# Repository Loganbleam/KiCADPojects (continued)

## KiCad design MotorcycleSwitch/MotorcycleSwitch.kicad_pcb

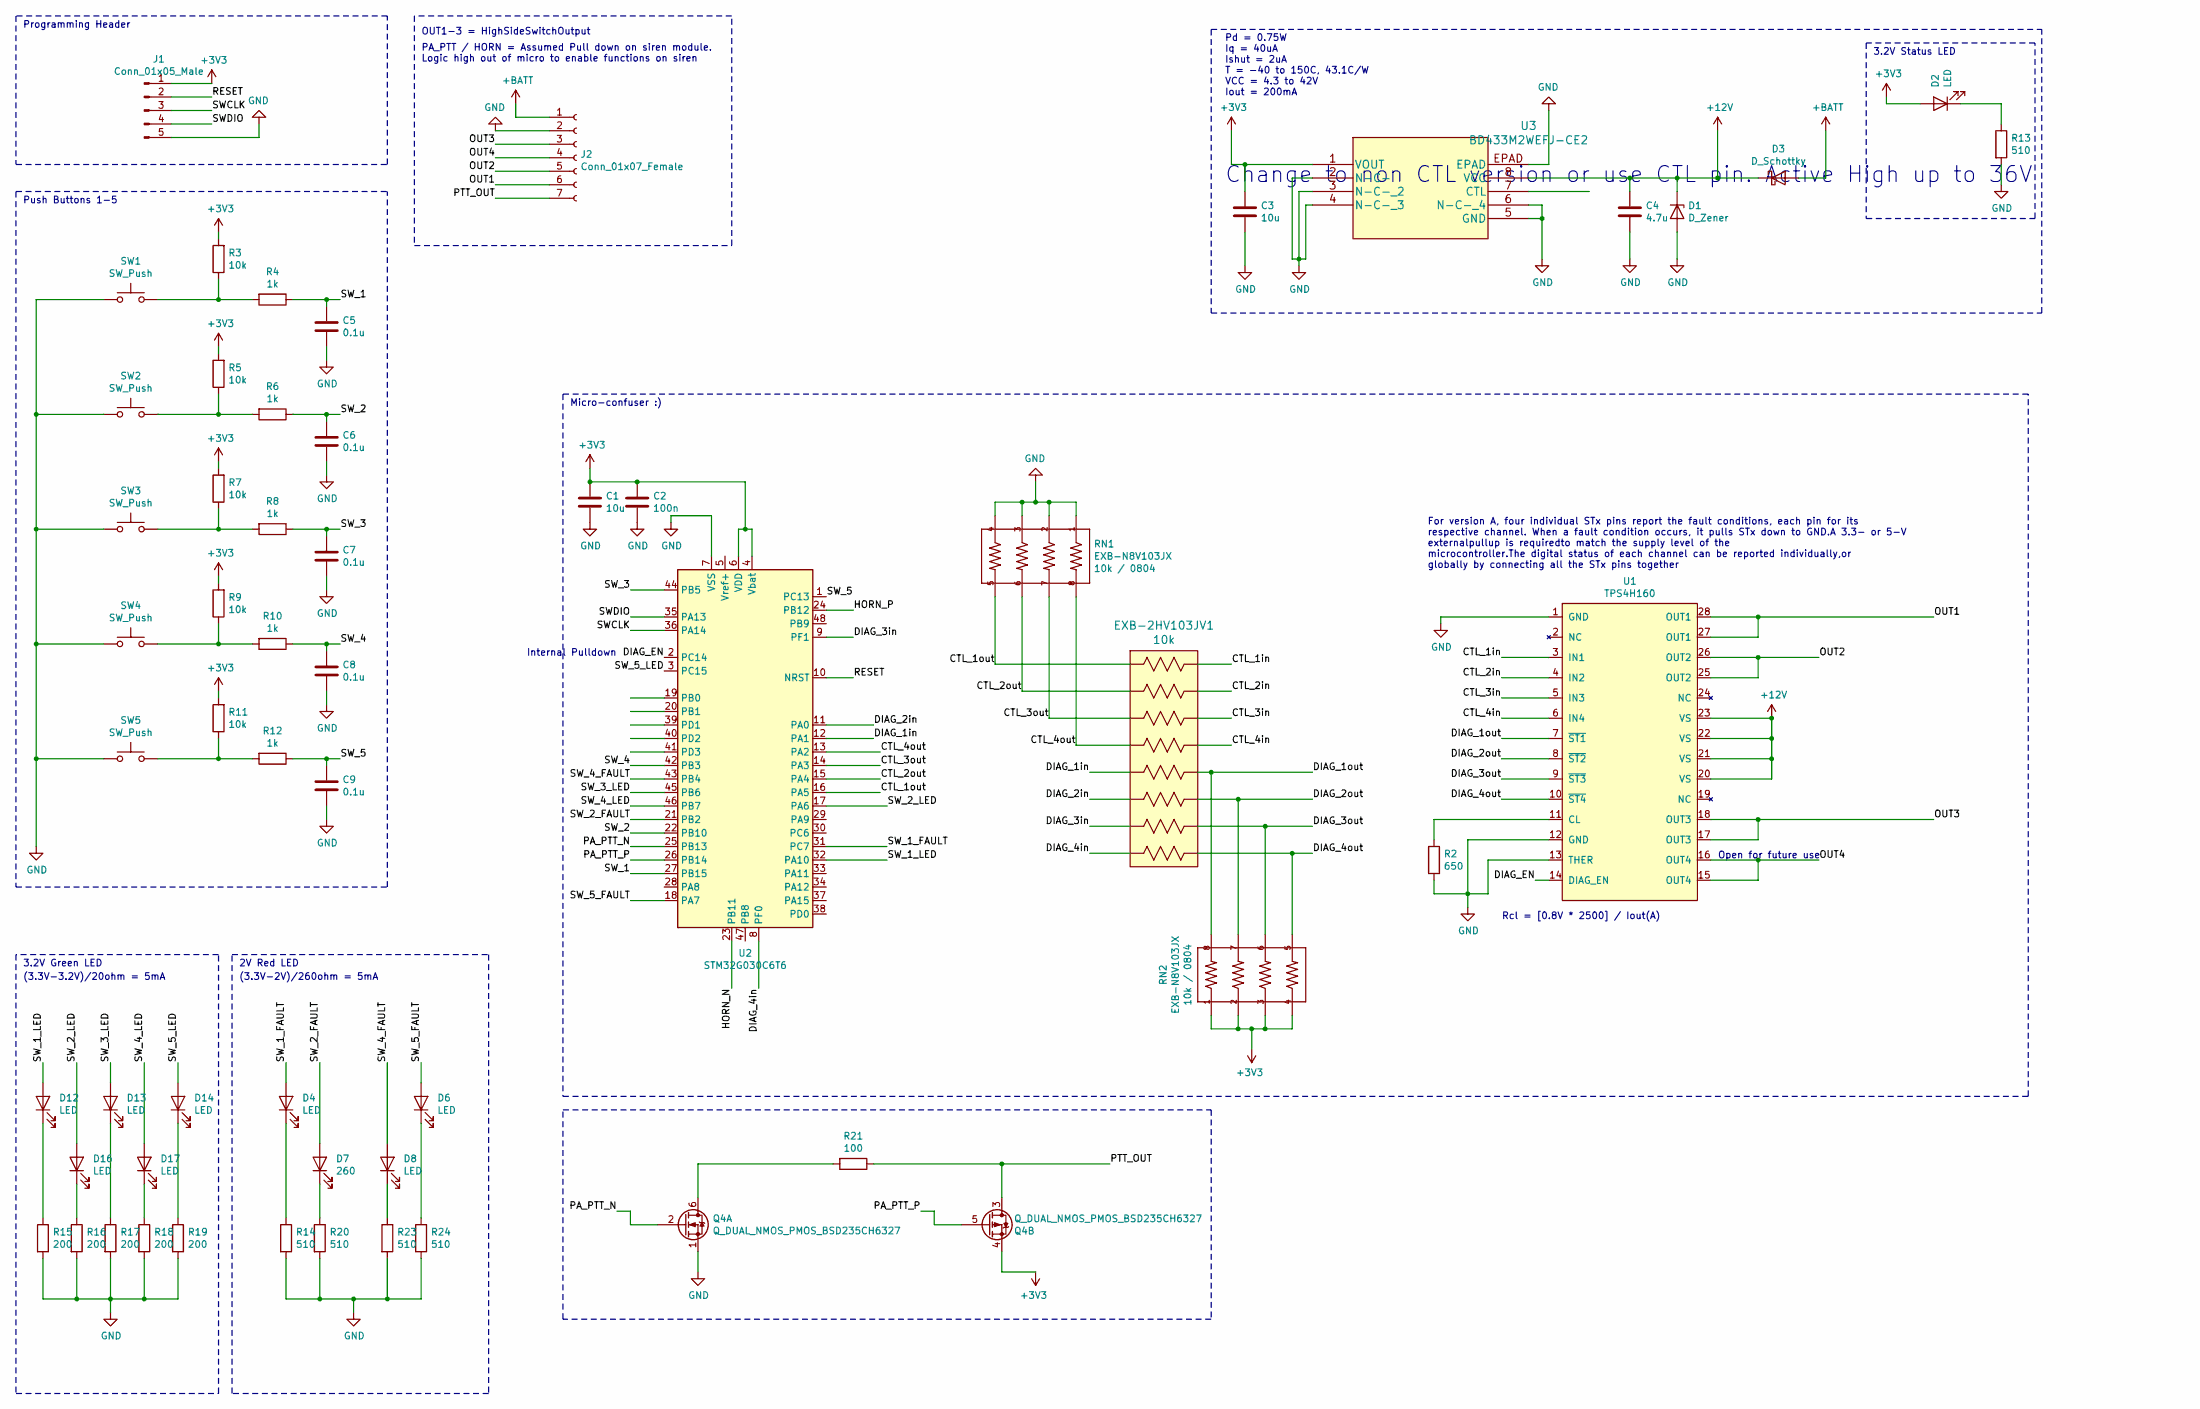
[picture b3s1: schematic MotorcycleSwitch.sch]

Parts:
C1, C3: 10u; C_0603_1608Metric
C2: 100n; C_0603_1608Metric
C4: 4.7u; C_0603_1608Metric
C5, C6, C7, C8, C9: 0.1u; C_0603_1608Metric
D1: D_Zener; D_SOD-123
D2: LED; LED_0603_1608Metric_Castellated
D3: D_Schottky; D_SMA
D4, D6, D8, D12, D13, D14, D16, D17: LED; LED_0603_1608Metric
D7: 260; LED_0603_1608Metric
EXB-2HV103JV1: 10k; EXB-2HV103JV
J1: Conn_01x05_Male; PinHeader_1x05_P2.54mm_Vertical
J2: Conn_01x07_Female; PinHeader_1x07_P2.54mm_Vertical
Q4: Q_DUAL_NMOS_PMOS_BSD235CH6327; SOT-363_SC-70-6
R2: 650; R_0603_1608Metric_Pad1.05x0.95mm_HandSolder
R3, R5, R7, R9, R11: 10k; R_0603_1608Metric
R4, R6, R8, R10, R12: 1k; R_0603_1608Metric
R13, R14, R20, R23, R24: 510; R_0603_1608Metric
R15, R16, R17, R18, R19: 200; R_0603_1608Metric
R21: 100; R_0603_1608Metric
RN1, RN2: EXB-N8V103JX
SW1, SW2, SW3, SW4, SW5: SW_Push; TL3305BF260QG
U1: TPS4H160; TPS4H160AQPWPRQ1
U2: STM32G030C6T6; LQFP-48_7x7mm_P0.5mm
U3: BD433M2WEFJ-CE2; BD433M2EFJ-CE2

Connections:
+3V3: C1.1, C2.1, C3.1, D2.2 (A), J1.1, Q4.4 (D), R3.2, R5.2, R7.2, R9.2, R11.2, RN2.1, RN2.2, RN2.3, RN2.4, U2.4 (Vbat), U2.6 (VDD), U3.1 (VOUT); also elsewhere on the board
+12V: C4.1, D1.1 (K), D3.1 (K), U1.20 (VS), U1.21 (VS), U1.22 (VS), U1.23 (VS), U3.8 (VCC)
+BATT: D3.2 (A), J2.1
/CTL_1in: EXB-2HV103JV1.16, U1.3 (IN1)
/CTL_1out: EXB-2HV103JV1.1, RN1.5, U2.16 (PA5)
/CTL_2in: EXB-2HV103JV1.15, U1.4 (IN2)
/CTL_2out: EXB-2HV103JV1.2, RN1.6, U2.15 (PA4)
/CTL_3in: EXB-2HV103JV1.14, U1.5 (IN3)
/CTL_3out: EXB-2HV103JV1.3, RN1.7, U2.14 (PA3)
/CTL_4in: EXB-2HV103JV1.13, U1.6 (IN4)
/CTL_4out: EXB-2HV103JV1.4, RN1.8, U2.13 (PA2)
/DIAG_1in: EXB-2HV103JV1.5, U2.12 (PA1)
/DIAG_1out: EXB-2HV103JV1.12, RN2.8, U1.7 (~ST1)
/DIAG_2in: EXB-2HV103JV1.6, U2.11 (PA0)
/DIAG_2out: EXB-2HV103JV1.11, RN2.7, U1.8 (~ST2)
/DIAG_3in: EXB-2HV103JV1.7, U2.9 (PF1)
/DIAG_3out: EXB-2HV103JV1.10, RN2.6, U1.9 (~ST3)
/DIAG_4in: EXB-2HV103JV1.8, U2.8 (PF0)
/DIAG_4out: EXB-2HV103JV1.9, RN2.5, U1.10 (~ST4)
/DIAG_EN: U1.14 (DIAG_EN), U2.2 (PC14)
/HORN_N: U2.23 (PB11); also elsewhere on the board
/HORN_P: U2.24 (PB12); also elsewhere on the board
/OUT1: J2.6, U1.27 (OUT1), U1.28 (OUT1)
/OUT2: J2.5, U1.25 (OUT2), U1.26 (OUT2)
/OUT3: J2.3, U1.17 (OUT3), U1.18 (OUT3)
/PA_PTT_N: Q4.2 (G), U2.25 (PB13)
/PA_PTT_P: Q4.5 (G), U2.26 (PB14)
/PTT_OUT: J2.7, Q4.3 (S), R21.1
/RESET: J1.2, U2.10 (NRST)
/SWCLK: J1.3, U2.36 (PA14)
/SWDIO: J1.4, U2.35 (PA13)
/SW_1: C5.1, R4.1, U2.27 (PB15)
/SW_1_FAULT: D4.2 (A), U2.31 (PC7)
/SW_1_LED: D12.2 (A), U2.32 (PA10)
/SW_2: C6.1, R6.1, U2.22 (PB10)
/SW_2_FAULT: D7.2 (A), U2.21 (PB2)
/SW_2_LED: D16.2 (A), U2.17 (PA6)
/SW_3: C7.1, R8.1, U2.44 (PB5)
/SW_3_LED: D13.2 (A), U2.45 (PB6)
/SW_4: C8.1, R10.1, U2.42 (PB3)
/SW_4_FAULT: D8.2 (A), U2.43 (PB4)
/SW_4_LED: D17.2 (A), U2.46 (PB7)
/SW_5: C9.1, R12.1, U2.1 (PC13)
/SW_5_FAULT: D6.2 (A), U2.18 (PA7)
/SW_5_LED: D14.2 (A), U2.3 (PC15)
GND: C1.2, C2.2, C3.2, C4.2, C5.2, C6.2, C7.2, C8.2, C9.2, D1.2 (A), J1.5, J2.2, Q4.1 (S), R2.2, R13.2, R14.2, R15.2, R16.2, R17.2, R18.2, R19.2, R20.2, R23.2, R24.2, RN1.1, RN1.2, RN1.3, RN1.4, SW1.1, SW2.1, SW3.1, SW4.1, SW5.1, U1.1 (GND), U1.12 (GND), U1.13 (THER), U2.7 (VSS), U3.2 (N-C-), U3.3 (N-C-_2), U3.4 (N-C-_3), U3.5 (GND), U3.6 (N-C-_4), U3.EPAD; also elsewhere on the board
unnamed: D2.1 (K), R13.1
unnamed: D4.1 (K), R14.1
unnamed: D6.1 (K), R24.1
unnamed: D7.1 (K), R20.1
unnamed: D8.1 (K), R23.1
unnamed: D12.1 (K), R15.1
unnamed: D13.1 (K), R17.1
unnamed: D14.1 (K), R19.1
unnamed: D16.1 (K), R16.1
unnamed: D17.1 (K), R18.1
unnamed: Q4.6 (D), R21.2
unnamed: R2.1, U1.11 (CL)
unnamed: R3.1, R4.2, SW1.2
unnamed: R5.1, R6.2, SW2.2
unnamed: R7.1, R8.2, SW3.2
unnamed: R9.1, R10.2, SW4.2
unnamed: R11.1, R12.2, SW5.2

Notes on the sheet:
For version A, four individual STx pins report the fault conditions, each pin for its respective channel. When a fault condition occurs, it pulls STx down to GND.A 3.3- or 5-V externalpullup is requiredto match the supply level of the microcontroller.The digital status of each channel can be report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
Rcl = [0.8V * 2500] / Iout(A)
2V Red LED
3.2V Green LED
Pd = 0.75W Iq = 40uA Ishut = 2uA T = -40 to 150C, 43.1C/W VCC = 4.3 to 42V Iout = 200mA
3.2V Status LED
Internal Pulldown
(3.3V-3.2V)/20ohm = 5mA
(3.3V-2V)/260ohm = 5mA
Open for future use
Push Buttons 1-5
Micro-confuser :)
Programming Header
OUT1-3 = HighSideSwitchOutput
PA_PTT / HORN = Assumed Pull down on siren module. Logic high out of micro to enable functions on siren
Change to non CTL version or use CTL pin. Active High up to 36V

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
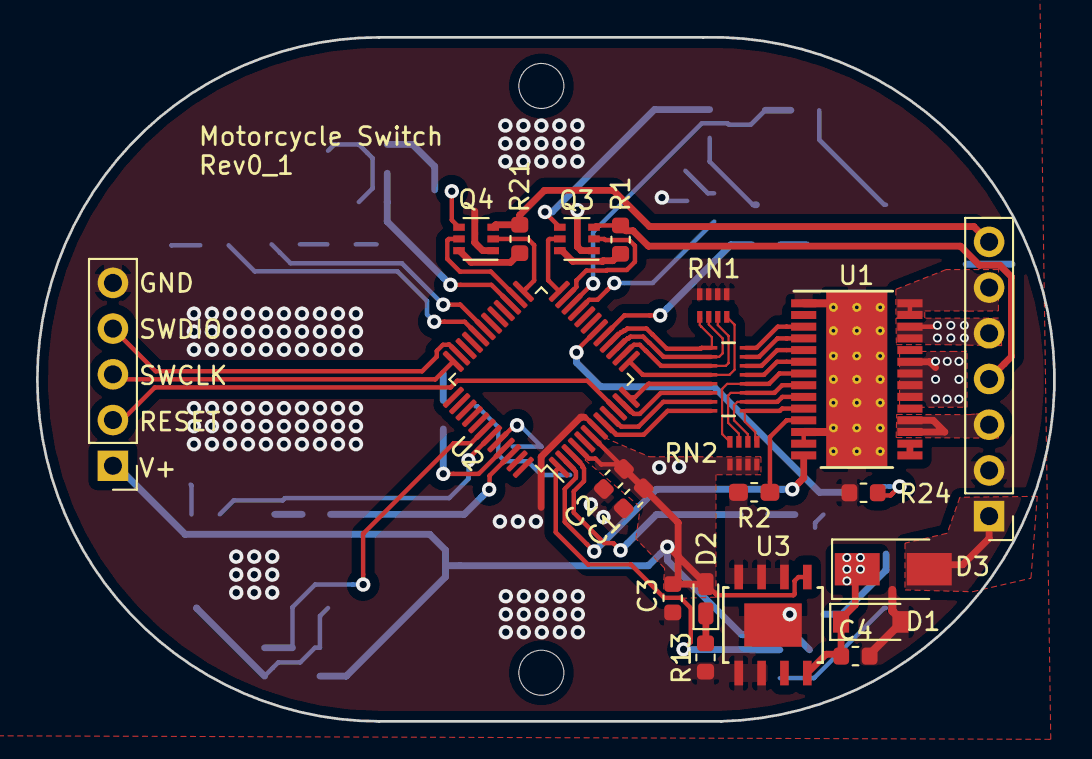
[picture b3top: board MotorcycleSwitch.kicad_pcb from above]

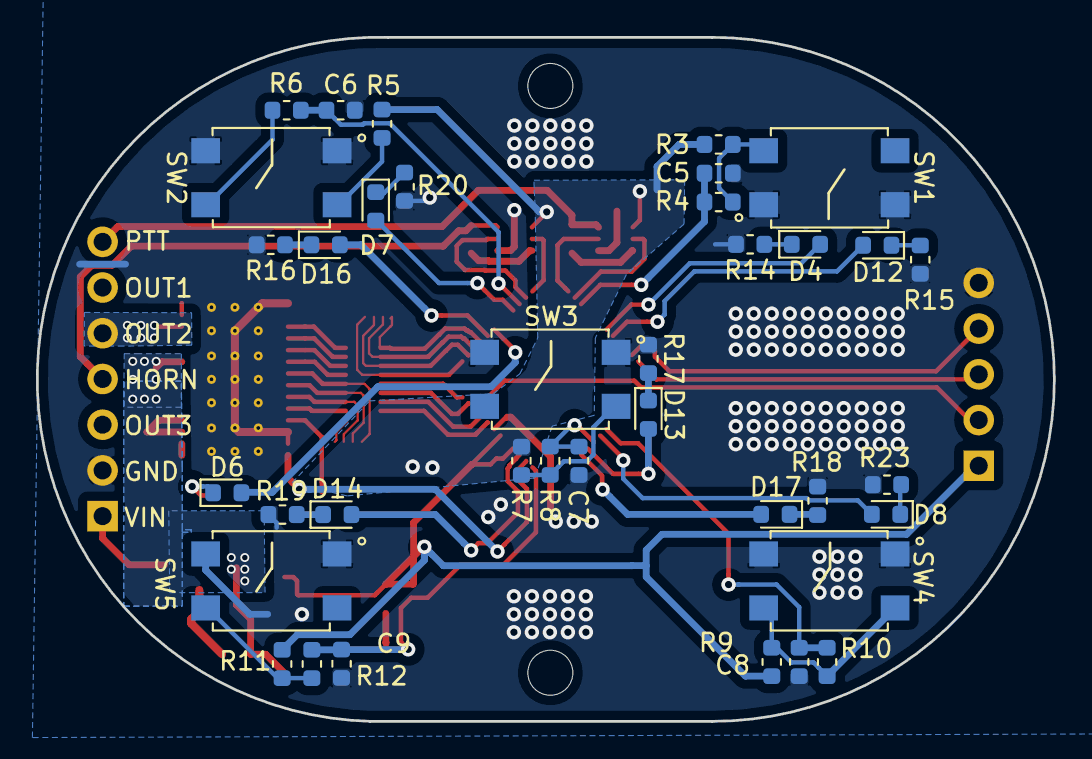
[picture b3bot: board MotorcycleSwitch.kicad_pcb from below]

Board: 2 copper layers, 56.5 x 38.0 mm, 59 parts (37 on the bottom side), 66 nets.

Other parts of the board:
Q3: Q_DUAL_NMOS_PMOS_BSD235CH6327; SOT-363_SC-70-6
R1: 100; R_0603_1608Metric

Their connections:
+3V3: Q3.4; also elsewhere on the board
/HORN_N: Q3.2; also elsewhere on the board
/HORN_P: Q3.5; also elsewhere on the board
GND: Q3.1; also elsewhere on the board
unnamed: Q3.6, R1.2

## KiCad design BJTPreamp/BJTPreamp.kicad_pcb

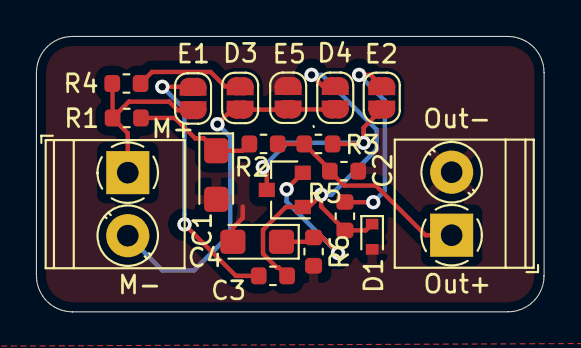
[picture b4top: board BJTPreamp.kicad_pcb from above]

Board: 2 copper layers, 28.2 x 15.3 mm, 19 parts (0 on the bottom side), 11 nets.

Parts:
C1, C4: CP; CP_EIA-3216-18_Kemet-A
C2, C3: C; C_0603_1608Metric
D1: D_TVS; D_SOD-523
D3, D4: SolderJumper_2_Open; SolderJumper-2_P1.3mm_Open_RoundedPad1.0x1.5mm
E1, E2, E5: SolderJumper_2_Open; SolderJumper-2_P1.3mm_Open_RoundedPad1.0x1.5mm
J1, J2: Conn_01x02_Male; TerminalBlock_Phoenix_PT-1,5-2-3.5-H_1x02_P3.50mm_Horizontal
Q1: MMBT3904; SOT-23
R1, R2, R3, R4, R5, R6: R; R_0603_1608Metric

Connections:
GND: C1.2, C2.2, C4.2, D1.2, E5.2, J2.2, R6.2
unnamed: C1.1, R1.1, R2.2
unnamed: C2.1, J2.1, R2.1, R3.1
unnamed: C3.1, D1.1, D4.2, Q1.1, R5.2
unnamed: C3.2, E1.2
unnamed: C4.1, Q1.2, R6.1
unnamed: E1.1, J1.1, R1.2, R4.1
unnamed: D3.1, D4.1, E5.1, J1.2
unnamed: E2.1, R5.1
unnamed: E2.2, Q1.3, R3.2
unnamed: D3.2, R4.2

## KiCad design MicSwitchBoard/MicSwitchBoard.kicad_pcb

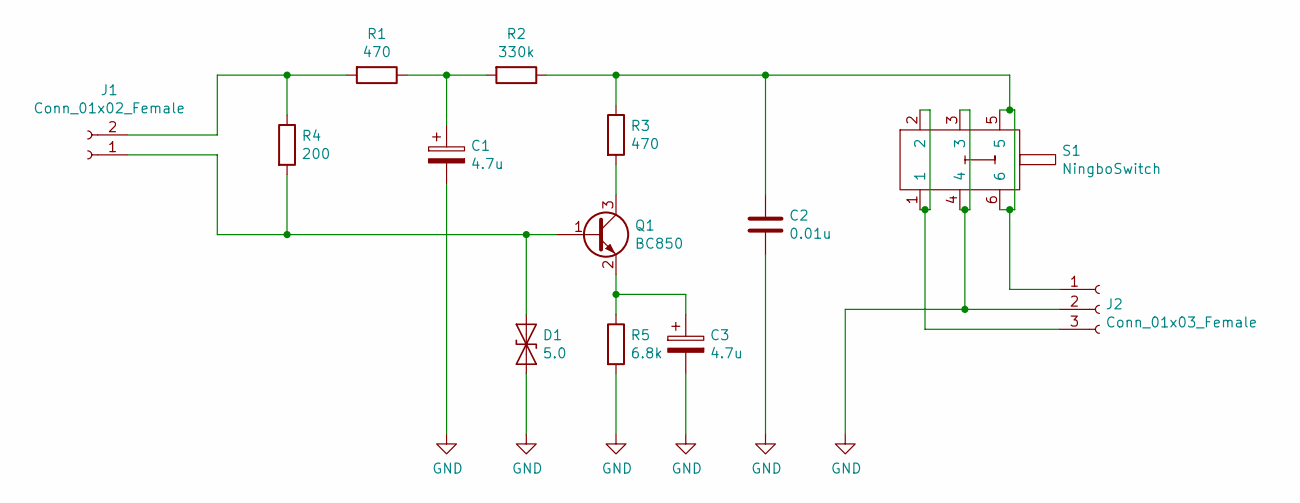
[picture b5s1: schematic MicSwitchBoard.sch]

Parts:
C1, C3: 4.7u; CP_Elec_4x4.5
C2: 0.01u; C_0603_1608Metric
D1: 5.0; D_SOD-523
J1: Conn_01x02_Female; PinHeader_1x02_P2.54mm_Vertical
J2: Conn_01x03_Female; PinHeader_1x03_P2.54mm_Vertical
Q1: BC850; SOT-23
R1, R3: 470; R_0603_1608Metric
R2: 330k; R_0603_1608Metric
R4: 200; R_0603_1608Metric
R5: 6.8k; R_0603_1608Metric
S1: NingboSwitch

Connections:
GND: C1.2, C2.2, C3.2, D1.1 (A1), J2.2, R5.2, S1.3, S1.4
unnamed: C1.1, R1.1, R2.2
unnamed: C2.1, J2.1, R2.1, R3.1, S1.5, S1.6
unnamed: C3.1, Q1.2 (E), R5.1
unnamed: D1.2 (A2), J1.1, Q1.1 (B), R4.2
unnamed: J1.2, R1.2, R4.1
unnamed: J2.3, S1.1, S1.2
unnamed: Q1.3 (C), R3.2

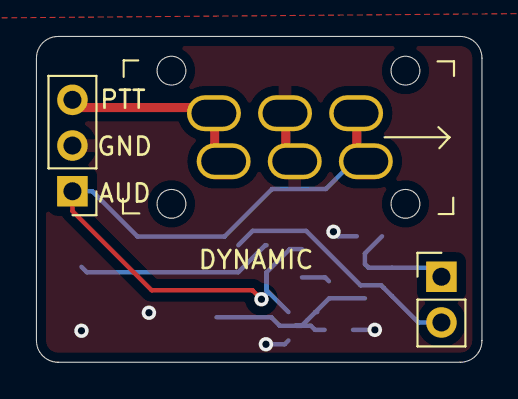
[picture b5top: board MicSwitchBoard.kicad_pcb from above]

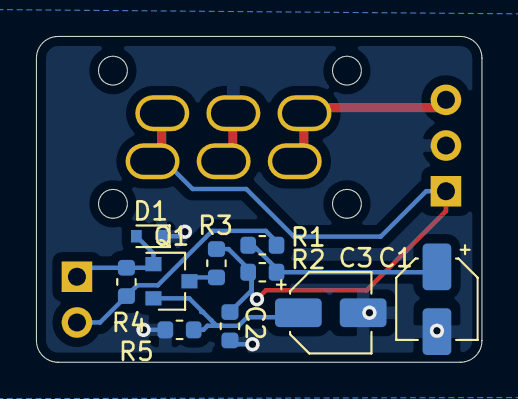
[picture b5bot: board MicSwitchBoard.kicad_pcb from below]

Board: 2 copper layers, 24.8 x 18.1 mm, 13 parts (10 on the bottom side), 8 nets.

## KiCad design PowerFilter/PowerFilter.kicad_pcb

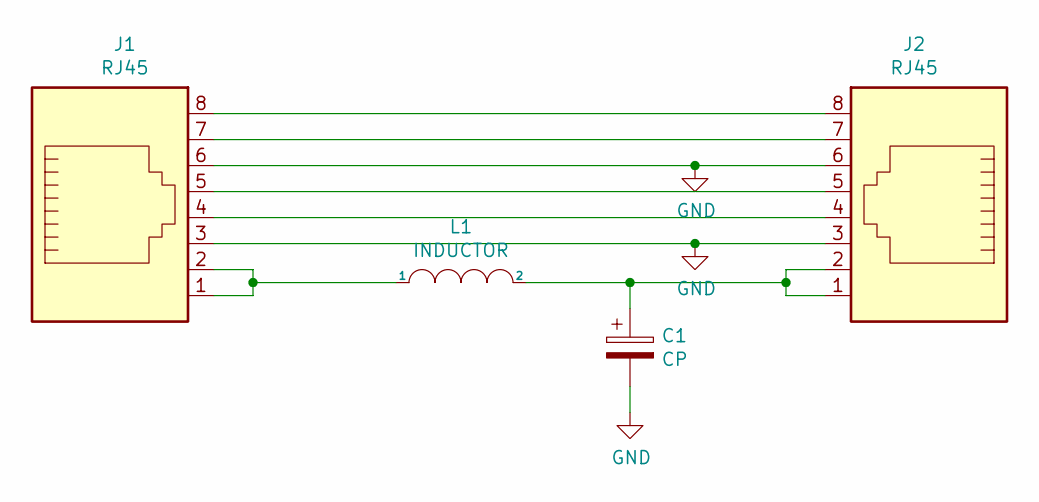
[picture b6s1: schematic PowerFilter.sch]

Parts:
C1: CP; CP_Radial_D22.0mm_P10.00mm_SnapIn
J1, J2: RJ45; RJ45_Amphenol_54602-x08_Horizontal
L1: INDUCTOR; 1410606C

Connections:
GND: C1.2, J1.3, J1.6, J2.3, J2.6
unnamed: C1.1, J2.1, J2.2, L1.2
unnamed: J1.1, J1.2, L1.1
unnamed: J1.4, J2.4
unnamed: J1.5, J2.5
unnamed: J1.7, J2.7
unnamed: J1.8, J2.8

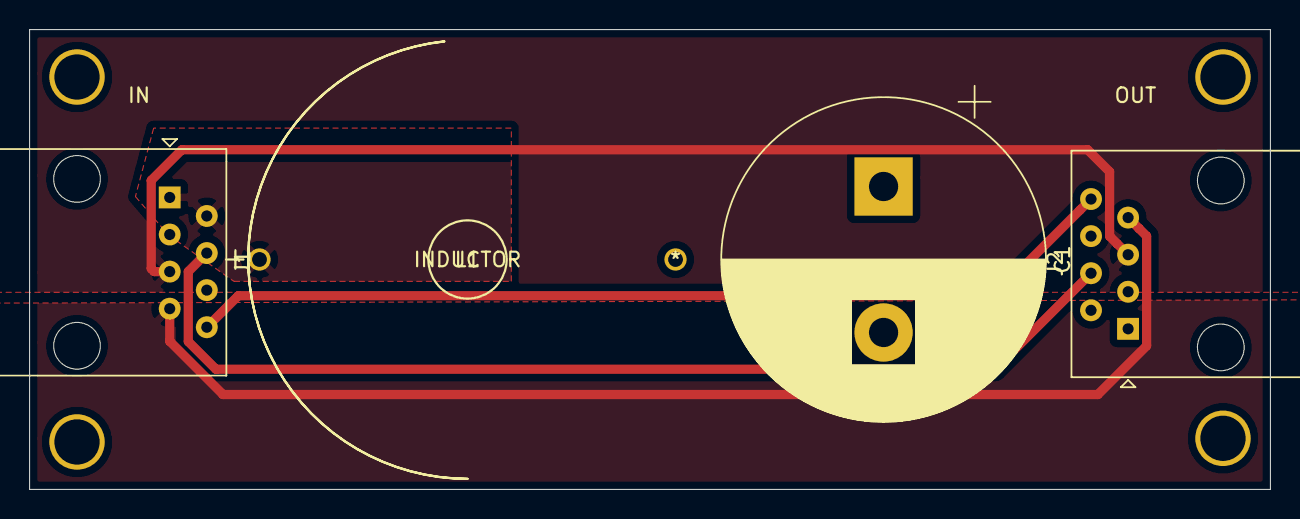
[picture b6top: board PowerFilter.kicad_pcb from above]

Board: 2 copper layers, 85.0 x 31.5 mm, 4 parts (0 on the bottom side), 7 nets.

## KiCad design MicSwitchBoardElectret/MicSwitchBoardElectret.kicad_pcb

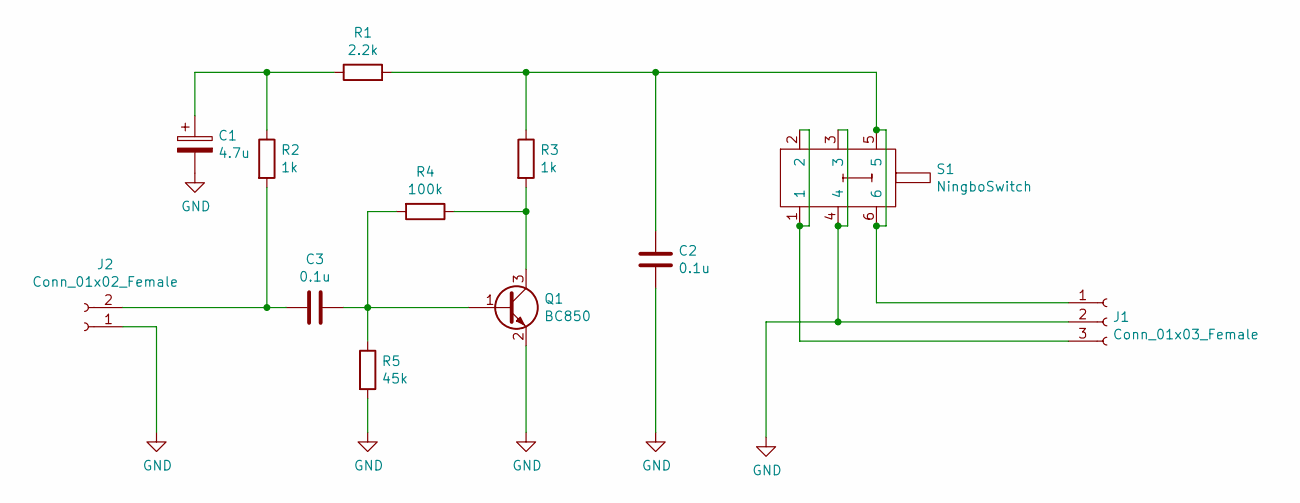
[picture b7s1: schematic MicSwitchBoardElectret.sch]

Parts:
C1: 4.7u; CP_Elec_4x4.5
C2, C3: 0.1u; C_0603_1608Metric
J1: Conn_01x03_Female; PinHeader_1x03_P2.54mm_Vertical
J2: Conn_01x02_Female; PinHeader_1x02_P2.54mm_Vertical
Q1: BC850; SOT-23
R1: 2.2k; R_0603_1608Metric
R2, R3: 1k; R_0603_1608Metric
R4: 100k; R_0603_1608Metric
R5: 45k; R_0603_1608Metric
S1: NingboSwitch

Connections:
GND: C1.2, C2.2, J1.2, J2.1, Q1.2 (E), R5.2, S1.3, S1.4
unnamed: C1.1, R1.1, R2.1
unnamed: C2.1, J1.1, R1.2, R3.1, S1.5, S1.6
unnamed: C3.1, Q1.1 (B), R4.2, R5.1
unnamed: C3.2, J2.2, R2.2
unnamed: J1.3, S1.1, S1.2
unnamed: Q1.3 (C), R3.2, R4.1

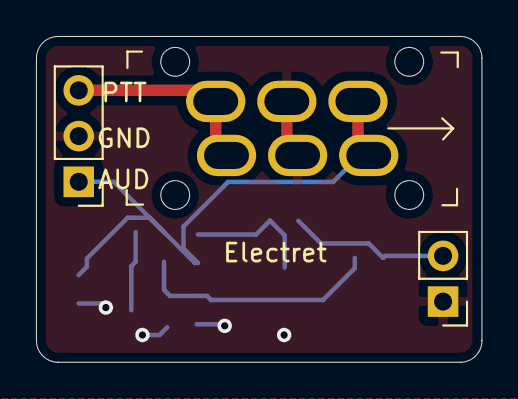
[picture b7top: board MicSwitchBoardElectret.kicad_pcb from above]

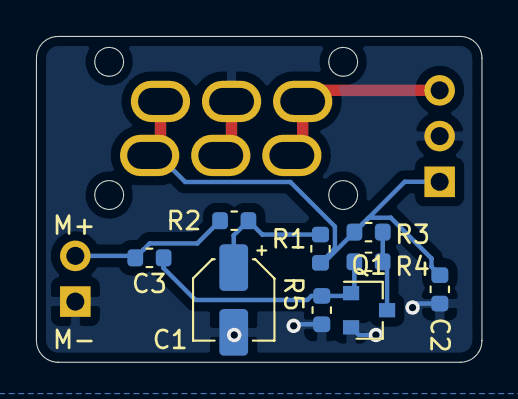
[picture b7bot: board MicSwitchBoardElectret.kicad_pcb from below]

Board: 2 copper layers, 24.8 x 18.1 mm, 12 parts (9 on the bottom side), 7 nets.

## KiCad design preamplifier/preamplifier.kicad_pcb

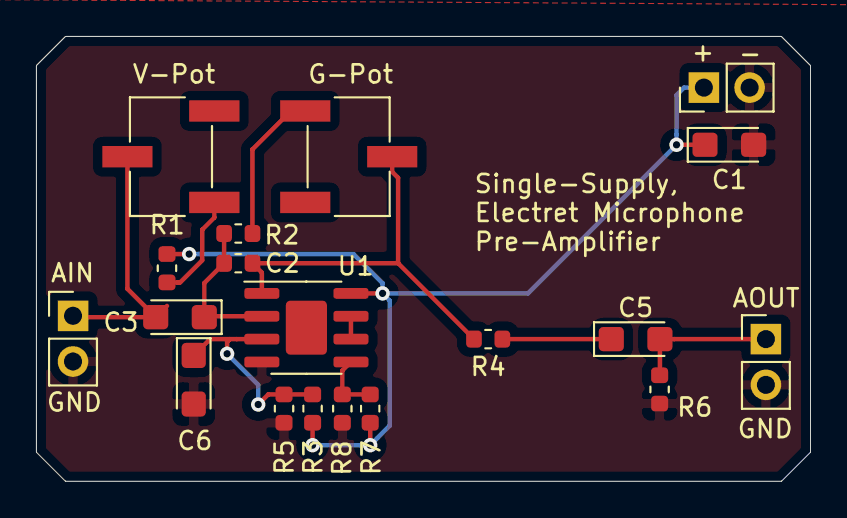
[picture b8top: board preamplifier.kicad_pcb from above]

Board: 2 copper layers, 43.0 x 24.7 mm, 19 parts (0 on the bottom side), 12 nets.

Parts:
C1: CP; CP_EIA-3216-18_Kemet-A
C2: 10p; C_0603_1608Metric
C3: 2.2uF; CP_EIA-3216-18_Kemet-A
C5, C6: 2.2u; CP_EIA-3216-18_Kemet-A
J1: Conn_Coaxial; PinHeader_1x02_P2.54mm_Vertical
J2, J3: Conn_01x02_Male; PinHeader_1x02_P2.54mm_Vertical
R1, R2: 2k; R_0603_1608Metric
R3, R5, R6, R8: 100k; R_0603_1608Metric
R4: 49.9; R_0603_1608Metric
R7: 75k; R_0603_1608Metric
RV1, RV2: R_POT; Potentiometer_Bourns_3269W_Vertical
U1: OPA1678; SOIC-8-1EP_3.9x4.9mm_P1.27mm_EP2.29x3mm

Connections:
+9V: C1.1, J3.1, R1.1, R3.1, R7.1, U1.8
/A_I: C3.2, J2.1, RV1.2
/A_O: C5.2, J1.1, R6.1
GND: C1.2, C6.2, J1.2, J2.2, J3.2, R5.2, R6.2, R8.2, U1.4
unnamed: C2.1, R4.2, RV2.2, U1.1
unnamed: C2.2, C3.1, R2.1, U1.2
unnamed: C5.1, R4.1
unnamed: C6.1, R3.2, R5.1, U1.3
unnamed: R1.2, RV1.1
unnamed: R2.2, RV2.1
unnamed: R7.2, R8.1, U1.5
unnamed: U1.6, U1.7

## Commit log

2020-04-13 Second commit
2020-04-15 push from desktop
2020-04-15 removed proj
2020-04-21 Desktop
2020-04-25 Laptop Push
2020-04-25 Desktop push
2020-05-30 Laptop
